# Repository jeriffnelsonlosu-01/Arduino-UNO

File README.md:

# Arduino-UNO
Arduino Uno board recreated in KiCad, including the schematic and PCB layout for learning and hardware design practice.

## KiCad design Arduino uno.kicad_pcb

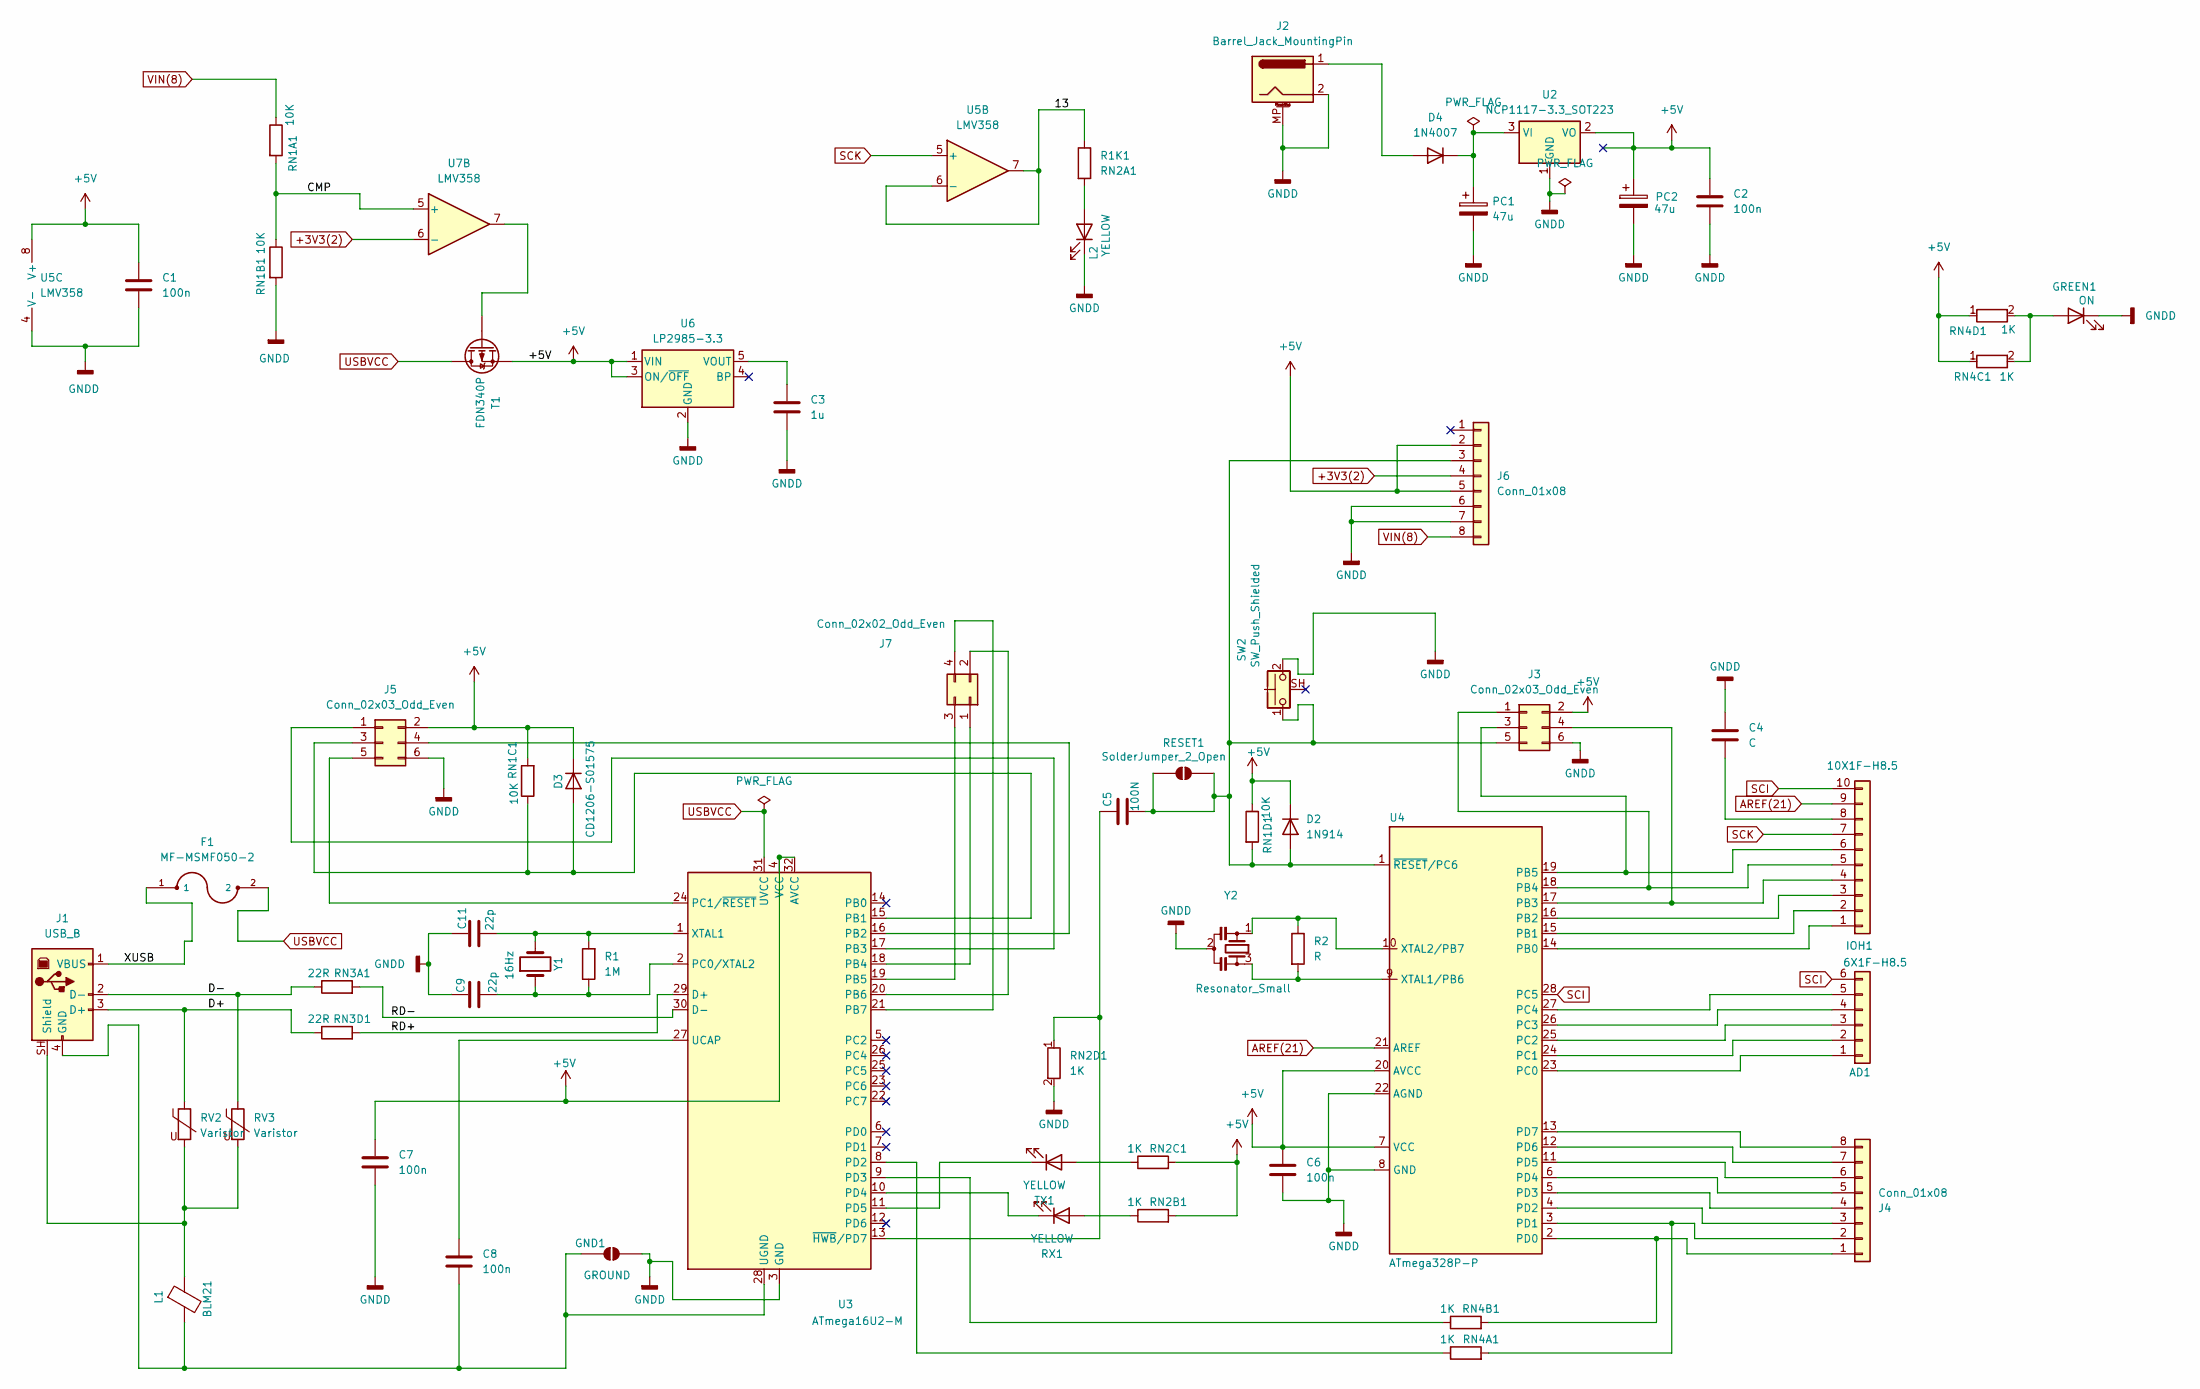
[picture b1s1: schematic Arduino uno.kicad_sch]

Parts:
AD1: 6X1F-H8.5; PinSocket_1x06_P2.54mm_Vertical
C1, C6, C7, C8: 100n; C_0603_1608Metric_Pad1.08x0.95mm_HandSolder
C2: 100n; C_0805_2012Metric_Pad1.18x1.45mm_HandSolder
C3: 1u; C_01005_0402Metric
C4: C; C_0603_1608Metric_Pad1.08x0.95mm_HandSolder
C5: 100N; C_0603_1608Metric_Pad1.08x0.95mm_HandSolder
C9, C11: 22p; C_0603_1608Metric_Pad1.08x0.95mm_HandSolder
D2: 1N914; D_SOD-123
D3: CD1206-S01575; D_SOD-123
D4: 1N4007; D_DO-41_SOD81_P7.62mm_Horizontal
F1: MF-MSMF050-2; FUSM4632X85
GND1: GROUND; SolderJumper-2_P1.3mm_Open_RoundedPad1.0x1.5mm
GREEN1: ON; LED_0805_2012Metric_Pad1.15x1.40mm_HandSolder
IOH1: 10X1F-H8.5; PinSocket_1x10_P2.54mm_Vertical
J1: USB_B; USB_B_TE_5787834_Vertical
J2: Barrel_Jack_MountingPin; BarrelJack_Horizontal
J3, J5: Conn_02x03_Odd_Even; PinHeader_2x03_P2.54mm_Vertical
J4, J6: Conn_01x08; PinSocket_1x08_P2.54mm_Vertical
J7: Conn_02x02_Odd_Even; PinHeader_2x02_P1.00mm_Vertical_SMD
L1: BLM21; L_0805_2012Metric_Pad1.05x1.20mm_HandSolder
L2: YELLOW; LED_0805_2012Metric_Pad1.15x1.40mm_HandSolder
PC1, PC2: 47u; CP_Elec_6.3x5.4
R1: 1M; R_0201_0603Metric_Pad0.64x0.40mm_HandSolder
R1K1: RN2A1; R_0201_0603Metric_Pad0.64x0.40mm_HandSolder
R2: R; R_0201_0603Metric_Pad0.64x0.40mm_HandSolder
RESET1: SolderJumper_2_Open; SolderJumper-2_P1.3mm_Open_RoundedPad1.0x1.5mm
RN1A1, RN1B1, RN1D1: 10K; R_0201_0603Metric_Pad0.64x0.40mm_HandSolder
RN1C1: 10K; R_0805_2012Metric_Pad1.20x1.40mm_HandSolder
RN2B1, RN2C1, RN2D1, RN4A1, RN4B1, RN4C1, RN4D1: 1K; R_0201_0603Metric_Pad0.64x0.40mm_HandSolder
RN3A1, RN3D1: 22R; R_0201_0603Metric_Pad0.64x0.40mm_HandSolder
RV2, RV3: Varistor; R_0201_0603Metric_Pad0.64x0.40mm_HandSolder
RX1: YELLOW; LED_0805_2012Metric_Pad1.15x1.40mm_HandSolder
SW2: SW_Push_Shielded; SW_Push_1P1T-MP_NO_Horizontal_Alps_SKRTLAE010
T1: FDN340P; SOT-23
TX1: YELLOW; LED_0805_2012Metric_Pad1.15x1.40mm_HandSolder
U2: NCP1117-3.3_SOT223; SOT-223-3_TabPin2
U3: ATmega16U2-M; QFN-32-1EP_5x5mm_P0.5mm_EP3.3x3.3mm
U4: ATmega328P-P; DIP-28_W7.62mm
U5, U7: LMV358; MSOP-8_3x3mm_P0.65mm
U6: LP2985-3.3; SOT-23-5
Y1: 16Hz; Crystal_HC49-4H_Vertical
Y2: Resonator_Small; Resonator_SMD_Murata_CSTxExxV-3Pin_3.0x1.1mm_HandSoldering

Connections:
+3V3(2): J6.4, U7.6 (-); also elsewhere on the board
+5V: C1.1, C2.1, C6.1, C7.1, D2.1 (K), D3.1 (K), J3.2, J5.2, J6.2, J6.5, PC2.1, RN1C1.2, RN1D1.1, RN2B1.2, RN2C1.2, RN4C1.1, RN4D1.1, T1.2 (S), U2.2 (VO), U3.4 (VCC), U3.32 (AVCC), U4.7 (VCC), U4.20 (AVCC), U5.8 (V+), U6.1 (VIN), U6.3 (ON/~OFF); also elsewhere on the board
/13: R1K1.1, U5.6 (-), U5.7; also elsewhere on the board
/CMP: RN1A1.2, RN1B1.1, U7.5 (+); also elsewhere on the board
/D+: J1.3 (D+), RN3D1.1, RV2.1
/D-: J1.2 (D-), RN3A1.1, RV3.1
/RD+: RN3D1.2, U3.29 (D+)
/RD-: RN3A1.2, U3.30 (D-)
/XUSB: F1.1, J1.1 (VBUS)
AREF(21): IOH1.9, U4.21 (AREF)
GNDD: C1.2, C2.2, C3.2, C4.2, C6.2, C7.2, C9.1, C11.1, GND1.2 (B), GREEN1.1 (K), J2.2, J2.MP (MountPin), J3.6, J5.6, J6.6, J6.7, L2.1 (K), PC1.2, PC2.2, RN1B1.2, RN2D1.2, SW2.2, U2.1 (GND), U3.3 (GND), U3.33 (GND), U4.8 (GND), U4.22 (AGND), U5.4 (V-), U6.2 (GND), Y2.2; also elsewhere on the board
unnamed: AD1.1, U4.23 (PC0)
unnamed: AD1.2, U4.24 (PC1)
unnamed: AD1.3, U4.25 (PC2)
unnamed: AD1.4, U4.26 (PC3)
unnamed: AD1.5, U4.27 (PC4)
unnamed: C5.2, D2.2 (A), J3.5, J6.3, RESET1.1 (A), RESET1.2 (B), RN1D1.2, SW2.1, U4.1 (~RESET/PC6)
unnamed: D3.2 (A), J5.3, RN1C1.1, U3.15 (PB1)
unnamed: D4.2 (A), J2.1
unnamed: D4.1 (K), PC1.1, U2.3 (VI)
unnamed: C8.2, GND1.1 (A), J1.4 (GND), L1.2, U3.28 (UGND)
unnamed: GREEN1.2 (A), RN4C1.2, RN4D1.2
unnamed: IOH1.1, U4.14 (PB0)
unnamed: IOH1.2, U4.15 (PB1)
unnamed: IOH1.3, U4.16 (PB2)
unnamed: IOH1.4, J3.4, U4.17 (PB3)
unnamed: IOH1.5, J3.1, U4.18 (PB4)
unnamed: IOH1.6, J3.3, U4.19 (PB5)
unnamed: C4.1, IOH1.8
unnamed: J1.SH (Shield), L1.1, RV2.2, RV3.2
unnamed: J4.1, RN4B1.2, U4.2 (PD0)
unnamed: J4.2, RN4A1.2, U4.3 (PD1)
unnamed: J4.3, U4.4 (PD2)
unnamed: J4.4, U4.5 (PD3)
unnamed: J4.5, U4.6 (PD4)
unnamed: J4.6, U4.11 (PD5)
unnamed: J4.7, U4.12 (PD6)
unnamed: J4.8, U4.13 (PD7)
unnamed: J5.1, U3.17 (PB3)
unnamed: J5.4, U3.16 (PB2)
unnamed: J5.5, U3.24 (PC1/~RESET)
unnamed: J7.1, U3.18 (PB4)
unnamed: J7.2, U3.20 (PB6)
unnamed: J7.3, U3.19 (PB5)
unnamed: J7.4, U3.21 (PB7)
unnamed: L2.2 (A), R1K1.2
unnamed: RN2B1.1, RX1.2 (A)
unnamed: RX1.1 (K), U3.10 (PD4)
unnamed 48: T1.1 (G), U7.7; also elsewhere on the board
unnamed: RN2C1.1, TX1.2 (A)
unnamed: TX1.1 (K), U3.11 (PD5)
unnamed: C9.2, R1.1, U3.2 (PC0/XTAL2), Y1.1
unnamed: RN4A1.1, U3.8 (PD2)
unnamed: RN4B1.1, U3.9 (PD3)
unnamed: C8.1, U3.27 (UCAP)
unnamed: C11.2, R1.2, U3.1 (XTAL1), Y1.2
unnamed: C5.1, RN2D1.1, U3.13 (~HWB/PD7)
unnamed: R2.2, U4.9 (XTAL1/PB6), Y2.3
unnamed: R2.1, U4.10 (XTAL2/PB7), Y2.1
unnamed: C3.1, U6.5 (VOUT)
SCI: AD1.6, IOH1.10, U4.28 (PC5)
SCK: IOH1.7, U5.5 (+); also elsewhere on the board
USBVCC: F1.2, T1.3 (D), U3.31 (UVCC)
VIN(8): J6.8, RN1A1.1

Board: 2 copper layers, 62 parts (0 on the bottom side), 64 nets, no tracks yet.

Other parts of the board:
U5#2, U5#3: LMV358; MSOP-8_3x3mm_P0.65mm

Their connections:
+3V3(2): U5#3.2 (-); also elsewhere on the board
+5V: U5#3.8 (V+); also elsewhere on the board
/13: U5#3.6 (-), U5#3.7; also elsewhere on the board
/CMP: U5#3.3 (+); also elsewhere on the board
GNDD: U5#3.4 (V-); also elsewhere on the board
unnamed 48: U5#3.1; also elsewhere on the board
SCK: U5#3.5 (+); also elsewhere on the board
